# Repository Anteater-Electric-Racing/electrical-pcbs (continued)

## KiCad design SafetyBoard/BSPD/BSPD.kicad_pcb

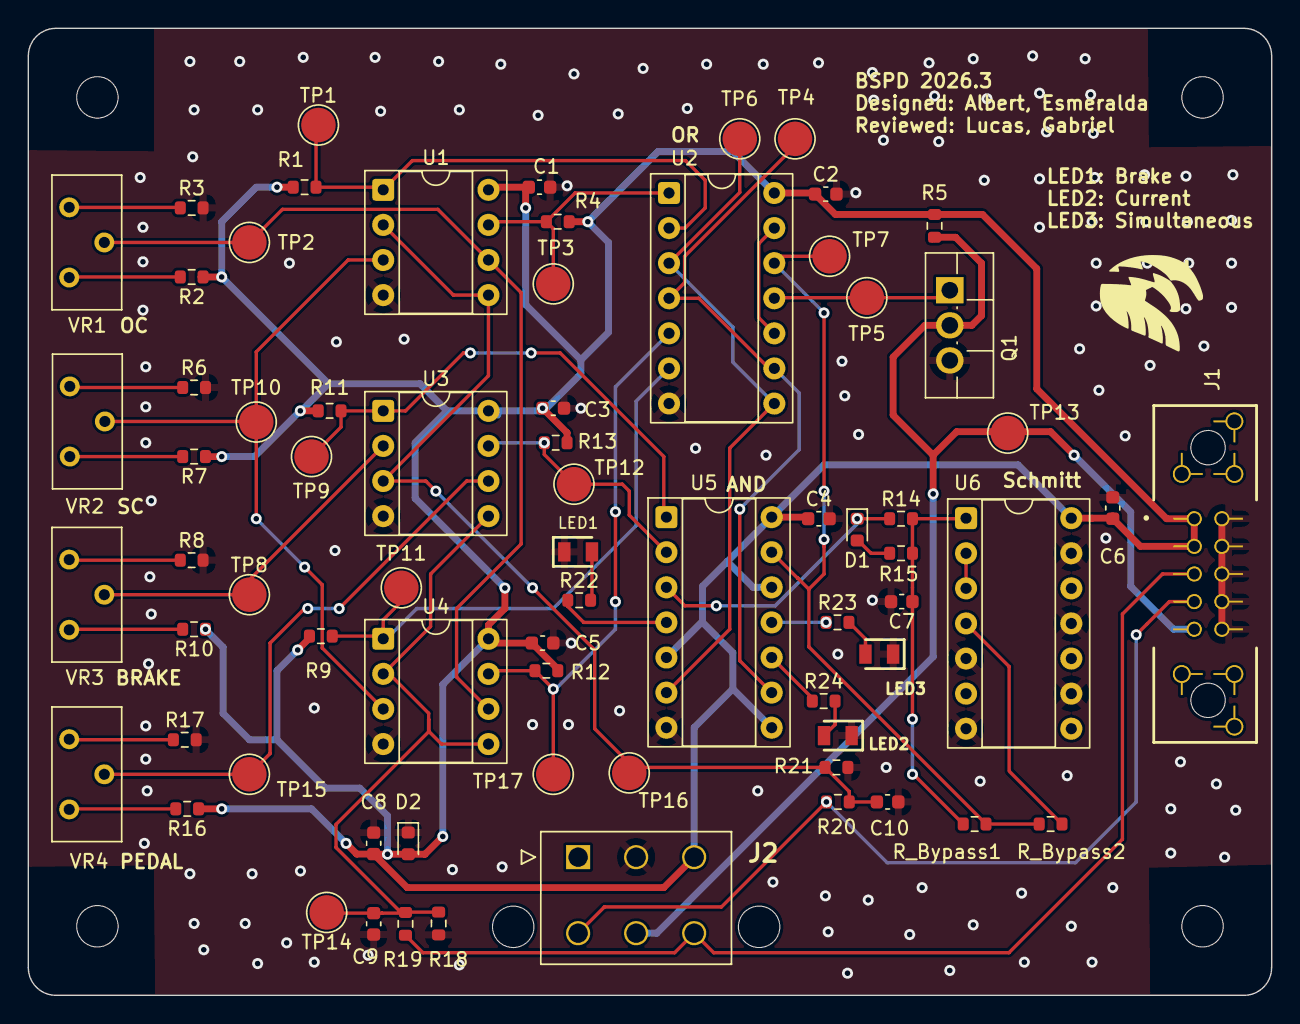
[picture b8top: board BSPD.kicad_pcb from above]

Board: 2 copper layers, 90.0 x 70.0 mm, 75 parts (0 on the bottom side), 41 nets.

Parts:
C1, C2, C3, C4, C5, C6: 0.1u; C_0603_1608Metric
C7: 3.3u; C_0603_1608Metric
C8: 10u; C_0603_1608Metric
C9, C10: 1n; C_0603_1608Metric
D1, D2: D; D_0603_1608Metric
H1, H2, H3, H4: MH; MountingHole_3mm
J1: T2M-105-01-X-D-TH-DS; SAMTEC_T2M-105-01-X-D-TH-DS
J2: 39-30-6068; 39-30-606Y
LED1, LED2, LED3: APTD2012LSYCK; LEDC2012X105N
Q1: IRLIZ44N NMOS; TO-220F-3_Vertical
R1, R4, R9, R11, R12, R13: 20k; R_0603_1608Metric
R2, R3, R6, R7, R8, R10, R16, R17: 10K; R_0603_1608Metric
R5, R22, R23, R24: 10k; R_0603_1608Metric
R14: 120k; R_0603_1608Metric
R15, R19, R20: 1k; R_0603_1608Metric
R18, R21: 500k; R_0603_1608Metric
R_Bypass1, R_Bypass2: 0; R_0603_1608Metric
TP1: B_SHORT; TestPoint_Pad_D2.5mm
TP2: OC; TestPoint_Pad_D2.5mm
TP3: B_OPEN; TestPoint_Pad_D2.5mm
TP4: P_ERROR; TestPoint_Pad_D2.5mm
TP5: FAULT_SENSED; TestPoint_Pad_D2.5mm
TP6: B_ERROR; TestPoint_Pad_D2.5mm
TP7: BOTH_ON; TestPoint_Pad_D2.5mm
TP8: BRAKE_TH; TestPoint_Pad_D2.5mm
TP9: B_APPLIED; TestPoint_Pad_D2.5mm
TP10: SC; TestPoint_Pad_D2.5mm
TP11: P_SHORT; TestPoint_Pad_D2.5mm
TP12: P_APPLIED; TestPoint_Pad_D2.5mm
TP13: BSPD_FAULT; TestPoint_Pad_D2.5mm
TP14: PEDAL; TestPoint_Pad_D2.5mm
TP15: PEDAL_TH; TestPoint_Pad_D2.5mm
TP16: BRAKE; TestPoint_Pad_D2.5mm
TP17: P_OPEN; TestPoint_Pad_D2.5mm
U1, U3, U4: LM393; DIP-8_W7.62mm_Socket
U2: 4071 4 Channel 2 Input OR gate; DIP-14_W7.62mm_Socket
U5: 4081 AND Gate; DIP-14_W7.62mm_Socket
U6: 40106 Inverter; DIP-14_W7.62mm_Socket
VR1, VR2, VR3, VR4: 3296Y-11-103LF; Potentiometer_Bourns_3296Y_Vertical

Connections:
+12V: C1.1, C2.1, C3.1, C4.1, C5.1, C6.1, C8.1, D2.2 (A), J1.01, J1.03, J2.3, R1.2, R2.1, R4.2, R5.1, R7.1, R9.2, R10.1, R11.2, R12.2, R13.2, R16.1, U1.8 (V+), U2.14 (VDD), U3.8 (V+), U4.8 (V+), U5.5, U5.8, U5.12, U5.14 (VDD), U6.14 (VDD)
BOTH_ON: R_Bypass1.2, R_Bypass2.1, TP7.1, U2.12, U5.13
BRAKE: C10.1, R20.1, R21.2, TP16.1, U1.2 (-), U1.5 (+), U3.3 (+)
BRAKE_APPLIED: R11.1, TP9.1, U3.1, U5.1
BRAKE_ERROR: TP6.1, U2.3, U2.8, U5.6
BRAKE_OPEN: R4.1, TP3.1, U1.7, U2.1
BRAKE_SHORT: R1.1, TP1.1, U1.1, U2.2
BRAKE_THRESHOLD: TP8.1, U3.2 (-), VR3.2 (WIPER)
BSPD_FAULT: J1.09, J2.5, Q1.2 (D), R5.2, TP13.1
B_IN: J1.07, J2.4, R20.2
CURRENT: C9.1, R18.2, R19.1, TP14.1, U3.5 (+), U4.2 (-), U4.5 (+)
C_IN: J1.05, J2.6, R19.2
FAULT_SENSED: Q1.1 (G), TP5.1, U2.11
GND: C1.2, C2.2, C3.2, C4.2, C5.2, C6.2, C7.2, C8.2, C9.2, C10.2, D2.1 (K), J1.02, J1.04, J1.06, J1.08, J1.10, J2.2, LED1.1 (K), LED2.1 (K), LED3.1 (K), Q1.3 (S), R3.2, R6.2, R8.2, R17.2, R18.1, R21.1, U1.4 (V-), U2.7 (VSS), U3.4 (V-), U4.4 (V-), U5.7 (VSS), U6.5, U6.7 (VSS), U6.9, U6.11, U6.13
unnamed: C7.1, R14.2, R15.2, R_Bypass1.1, U6.1
unnamed: D1.2 (A), R15.1
unnamed: D1.1 (K), R14.1, U5.3
unnamed: LED1.2 (A), R22.2
unnamed: LED2.2 (A), R24.2
unnamed: LED3.2 (A), R23.2
unnamed: R22.1, U5.4
unnamed: R23.1, U5.11
unnamed: R24.1, U5.10
unnamed: R_Bypass2.2, U6.4
unnamed: U2.10, U2.13
unnamed: U6.2, U6.3
unnamed: R3.1, VR1.1 (CCW)
unnamed: R2.2, VR1.3 (CW)
unnamed: R6.1, VR2.1 (CCW)
unnamed: R7.2, VR2.3 (CW)
unnamed: R8.1, VR3.1 (CCW)
unnamed: R10.2, VR3.3 (CW)
unnamed: R17.1, VR4.1 (CCW)
unnamed: R16.2, VR4.3 (CW)
OPEN_CIRCUIT: TP2.1, U1.6 (-), U4.6 (-), VR1.2 (WIPER)
PEDAL_APPLIED: R13.1, TP12.1, U3.7, U5.2
PEDAL_ERROR: TP4.1, U2.4, U2.9, U5.9
PEDAL_OPEN: R12.1, TP17.1, U2.5, U4.7
PEDAL_SHORT: R9.1, TP11.1, U2.6, U4.1
PEDAL_THRESHOLD: TP15.1, U3.6 (-), VR4.2 (WIPER)
SHORT_CIRCUIT: TP10.1, U1.3 (+), U4.3 (+), VR2.2 (WIPER)

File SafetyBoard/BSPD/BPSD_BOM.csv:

"Reference","Value","Datasheet","Footprint","Qty","DNP","Manufacturer_Part_Number","Manufacturer_Name"
"J2","39-30-6068","https://www.molex.com/pdm_docs/sd/039306048_sd.pdf","39-30:39-30-606Y","1","","39-30-6068","Molex"
"C1,C2,C3,C4,C5,C6","0.1u","https://www.mouser.com/ProductDetail/Murata-Electronics/GRT1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","Capacitor_SMD:C_0603_1608Metric","6","","GRT188R71H104KE13D ","Murata Electronics"
"C7","3.3u","https://www.digikey.com/en/products/detail/kemet/C0603C335K9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","Capacitor_SMD:C_0603_1608Metric","1","","C0603C335K9PACTU","Kemet"
"C8","10u","https://www.digikey.com/en/products/detail/murata-electronic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","Capacitor_SMD:C_0603_1608Metric","1","","GRM188R60J106KE47D","Murata Electronics"
"C9,C10","1n","https://www.mouser.com/ProductDetail/Murata-Electronics/GRM1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","Capacitor_SMD:C_0603_1608Metric","2","","GRM188R72E102KW07D","Murata Electronics "
"D1,D2","D","https://www.digikey.com/en/products/detail/bourns-inc/CD0603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","Diode_SMD:D_0603_1608Metric","2","","CD0603-B0240R","Bourns Inc"
"H1,H2,H3,H4","MH","~","MountingHole:MountingHole_3mm","4","","",""
"U2","4071 4 Channel 2 Input OR gate","http://www.intersil.com/content/dam/Intersil/documents/cd40/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","Package_DIP:DIP-14_W7.62mm_Socket","1","","CD4071BE","Texas Instruments"
"U5","4081 AND Gate","http://www.intersil.com/content/dam/Intersil/documents/cd40/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","Package_DIP:DIP-14_W7.62mm_Socket","1","","CD4081BEE4","Texas Instruments"
"U6","40106 Inverter","https://assets.nexperia.com/documents/data-sheet/HEF40106B.pdf","Package_DIP:DIP-14_W7.62mm_Socket","1","","CD40106BE ","Texas Instruments"
"U1,U3,U4","LM393","http://www.ti.com/lit/ds/symlink/lm393.pdf","Package_DIP:DIP-8_W7.62mm_Socket","3","","LM393P","Texas Instruments"
"Q1","IRLIZ44N NMOS","http://www.irf.com/product-info/datasheets/data/irliz44n.pdf","Package_TO_SOT_THT:TO-220F-3_Vertical","1","","IRLZ44NPBF","Infineon"
"VR1,VR2,VR3,VR4","3296Y-11-103LF","https://www.bourns.com/pdfs/3296.pdf","Potentiometer_THT:Potentiometer_Bourns_3296Y_Vertical","4","","3296Y-11-103LF","Bourns"
"R1,R4,R9,R11,R12,R13","20k","https://www.digikey.com/en/products/detail/yageo/RC0603FR-07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","Resistor_SMD:R_0603_1608Metric","6","","RC0603FR-0720KL","Yageo"
"R2,R3,R6,R7,R8,R10,R16,R17","10K","https://www.digikey.com/en/products/detail/yageo/RC0603FR-07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","Resistor_SMD:R_0603_1608Metric","8","","RC0603FR-0710KL","Yageo"
"R5,R22,R23,R24","10k","https://www.digikey.com/en/products/detail/yageo/RC0603FR-07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","Resistor_SMD:R_0603_1608Metric","4","","RC0603FR-0720KL","Yageo"
"R14","120k","https://www.digikey.com/en/products/detail/yageo/RC0603FR-07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","Resistor_SMD:R_0603_1608Metric","1","","RC0603FR-07120KL","Yageo"
"R15,R19,R20","1k","https://www.digikey.com/en/products/detail/yageo/RC0603FR-07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","Resistor_SMD:R_0603_1608Metric","3","","RC0603FR-071KL","Yageo"
"R18,R21","500k","https://www.digikey.com/en/products/detail/yageo/RC0603FR-07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","Resistor_SMD:R_0603_1608Metric","2","","RC0603FR-07500KL","Yageo"
"R_Bypass1,R_Bypass2","0","~","Resistor_SMD:R_0603_1608Metric","2","","","Yageo"
"LED1,LED2,LED3","APTD2012LSYCK","http://www.kingbrightusa.com/images/catalog/SPEC/APTD2012LSYCK.pdf","SMALL_LED:LEDC2012X105N","3","","APTD2012LSYCK","Kingbright"
"J1","T2M-105-01-X-D-TH-DS","","T2M_105:SAMTEC_T2M-105-01-X-D-TH-DS","1","","T2M-105-01-X-D-TH-DS","Samtec Inc."
"TP1","B_SHORT","~","TestPoint:TestPoint_Pad_D2.5mm","1","","",""
"TP2","OC","~","TestPoint:TestPoint_Pad_D2.5mm","1","","",""
"TP3","B_OPEN","","TestPoint:TestPoint_Pad_D2.5mm","1","","",""
"TP4","P_ERROR","~","TestPoint:TestPoint_Pad_D2.5mm","1","","",""
"TP5","FAULT_SENSED","~","TestPoint:TestPoint_Pad_D2.5mm","1","","",""
"TP6","B_ERROR","~","TestPoint:TestPoint_Pad_D2.5mm","1","","",""
"TP7","BOTH_ON","~","TestPoint:TestPoint_Pad_D2.5mm","1","","",""
"TP8","BRAKE_TH","~","TestPoint:TestPoint_Pad_D2.5mm","1","","",""
"TP9","B_APPLIED","~","TestPoint:TestPoint_Pad_D2.5mm","1","","",""
"TP10","SC","~","TestPoint:TestPoint_Pad_D2.5mm","1","","",""
"TP11","P_SHORT","~","TestPoint:TestPoint_Pad_D2.5mm","1","","",""
"TP12","P_APPLIED","~","TestPoint:TestPoint_Pad_D2.5mm","1","","",""
"TP13","BSPD_FAULT","~","TestPoint:TestPoint_Pad_D2.5mm","1","","",""
"TP14","PEDAL","~","TestPoint:TestPoint_Pad_D2.5mm","1","","",""
"TP15","PEDAL_TH","~","TestPoint:TestPoint_Pad_D2.5mm","1","","",""
"TP16","BRAKE","~","TestPoint:TestPoint_Pad_D2.5mm","1","","",""
"TP17","P_OPEN","~","TestPoint:TestPoint_Pad_D2.5mm","1","","",""

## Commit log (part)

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2025-11-13 Add standardized PCB structure with RTM and TSSI folders
2025-11-14 RTM KiCad Upload
2025-11-14 RTM File update
2025-11-20 PCC addition
2025-11-20 Create Kicad
2025-11-20 Create tempp
2025-11-20 Create temp
2025-11-20 Create tem
2025-11-20 Add Updated TSSI 2026.1
2025-12-02 2026.1 fixed vbias, removed nmos after r9, r10/r8 increased
2025-12-02 2026.1 fixed vbias, removed nmos after r9, r10/r8 increase
2025-12-02 schematic pdf
2025-12-22 Add PDB pcb
2025-12-22 Silkscreen pin assignment now easier
2025-12-23 Restored step files
2025-12-28 Updated throttle sensors, marked 24V components DNP
2025-12-28 Added labels for every net
2026-01-05 Started labeling each pin
2026-01-07 Combined break pressure into Throttle sensor
2026-01-07 Added labels of possibly removeing 3V3 line
2026-01-08 added BSPD v1
2026-01-08 pcb rules test
2026-01-08 Add 2026.2 TSSI
2026-01-08 Create 2026.2 Kicad
2026-01-08 Add TSSI 2026.2
2026-01-08 Create mosfet
2026-01-08 Add TSSI2026.2
2026-01-09 update kicad checklist
2026-01-09 draft2
2026-01-10 Added more silkscreen labels
2026-01-11 ver1 1/10/2026
2026-01-11 Added 24V line back
2026-01-13 Updated RTM silkscreen
2026-01-17 Latch Board Added
2026-01-19 Update BSPD documentation with parts list and corrections
2026-01-21 2026.1 RTM modifications
    includes justification for optocoupler change
2026-01-26 Create 2026.2CCM
    temp folder until I'm able to modify the CCM folder (unless this becomes the actual CCM folder). This temp folder holds the newest CCMv3 files as of 1/25/26
2026-01-26 Delete 2026.2CCM
    needed to make folder
2026-01-26 Create 2026CCM folder
    temp folder until I'm able to modify the other CCM folder (unless this becomes the actual CCM folder). This temp folder holds the newest CCMv3 files as of 1/25/26
2026-01-26 2026.2 CCMv3
    temp folder until I can modify the actual CCM folder. added sensors, changed pin assignment on Teensy, fixed speaker amplifier. Documentation of modifications included.
2026-01-26 moved to correct temp folder
2026-01-26 not needed
2026-01-28 adding new BSPD version as well as latch
2026-02-01 Update TSSI_2026.2
    Removed 12V for lights and condensed to 2 pin for one light and the other
2026-02-02 Add silkscreen connectors
2026-02-02 connected remaining pins to gnd
2026-02-02 add gerber files
2026-02-05 Add silkscreen
2026-02-05 add PCIE stuff
2026-02-09 RTM with Revisions told by Gabe
2026-02-10 corrected biasing network, moved Vin trace
    Vin trace stays out of electrical isolation zone
2026-02-10 Update documentation
2026-02-10 Added plated mounting holes, fixed diode
2026-02-10 Made quick changes: updated fuse footprint
2026-02-11 Change TSSI2026.3
    Deleted the whole schematic ong
2026-02-11 Finish Latch 2026.21
    Vasily did this :)
2026-02-11 Add Logo
2026-02-12 Gerber Files
2026-02-12 Updated silkscreen based on Gabe's revisions
2026-02-12 Shink overall board size for PDB
2026-02-12 Added logo to front silkscreen
2026-02-13 bspd v3 plus documentation
2026-02-13 adding logo plus updating documentation
2026-02-13 Add Logo again
2026-02-16 Updated silkscreen based on Gabe's revisions #2
    Fixed missing resistor (R15) on layout
2026-02-21 3d files
2026-02-21 export step
2026-02-21 add Molex Step Files
2026-02-21 Add latch step file
2026-02-21 PDB: Removed most 5V fuses, made board size smaller
2026-02-22 file tinkering for 3d
2026-02-24 reorganizing ccm folders
2026-02-24 Revert "reorganizing ccm folders"
    This reverts commit 4ae5fa8156d4e531640948b4a7b079df29438b2f.
2026-02-24 reorganizing ccm folders
    unlinked old ccm submodule, made new ccm folder, added ccm v2 to it as 2026.1 and ccm v3 as 2026.2
2026-02-24 Revert "reorganizing ccm folders"
    This reverts commit c6433f84ad807e394f1869382292bc8514728ac1.
2026-02-26 Major changes for PDB schematic
2026-02-26 Moved .gitignore from PDB to root
2026-02-28 Rename bbc/Hi_board_bbc1.kicad_prl to bbc/export1/Hi_board_bbc1.kicad_prl
2026-02-28 Add Hi_board_bbc1.kicad_pro to export1 directory
2026-02-28 Add Hi_board_bbc1.kicad_sch to export1 directory
2026-02-28 Add fp-info-cache to export1 directory
2026-02-28 Rename bbc/hi_bbc1_export.zip to bbc/export1/hi_bbc1_export.zip
2026-02-28 Remove lock file for Hi_board_bbc1 PCB
2026-02-28 Rename bbc/~Hi_board_bbc1.kicad_sch.lck to bbc/export1/~Hi_board_bbc1.kicad_sch.lck
2026-02-28 Update and rename bbc/sym-lib-table to bbc/libraries/sym-lib-table
2026-02-28 Add libraryBBC.kicad_sym to export2 directory
2026-02-28 Move sym-lib-table to export2 directory
2026-02-28 Update GLVMP_Banana_Jack.kicad_mod file location
2026-03-02 adding test plan draft
2026-03-02 adding test plan
2026-03-02 adding rules scripts
2026-03-07 added BSPD testing report
2026-03-07 added BSPD testing report v2
2026-03-07 editing test report format
2026-03-08 Redesign TSSI
2026-03-08 slight Tweaks again
2026-03-10 Changed all NMOS to GDS
2026-03-10 Swapped NMOS at bottom
2026-03-10 swaped pins on relay
2026-03-12 Rename bbc/4Pin Deutsch Connector.SLDPRT to bbc/ROC_CAD /4Pin Deutsch Connector.SLDPRT
2026-03-12 Rename bbc/BBC Assembly.SLDASM to bbc/ROC_CAD/BBC Assembly.SLDASM
2026-03-12 Rename 4Pin Deutsch Connector.SLDPRT to 4Pin Deutsch Connector.SLDPRT
2026-03-12 Rename bbc/BBC Container.SLDPRT to bbc/ROC_CAD/BBC Container.SLDPRT
2026-03-12 Rename bbc/Master Switch.SLDPRT to bbc/ROC_CAD/Master Switch.SLDPRT
2026-03-12 Rename bbc/Speaker.SLDPRT to bbc/ROC_CAD/Speaker.SLDPRT
2026-03-12 Update BSPD schematic and add BOM
2026-03-12 Add LATCH_BOM.csv
2026-03-12 Add TSSI BOM
2026-03-13 Deleted extra trace
2026-03-14 fixed comparator pinouts and pcb layout
2026-03-19 Reduced PDB size, power planes just started
2026-03-23 Finalized PDB silkscreen
2026-03-25 PDB Edits: Fixed 3D model, init README.md
2026-03-25 PDB: Started rough draft of README.md
2026-03-26 Add PCC
2026-03-26 deleted redundant PCC folder
2026-03-27 ARCHIVE: Snapshot of folder-based structure before flattening
2026-03-27 REORG: Flattened folder structure. we now use tags after every order to mark a finalized version. Keep overriding and pushing to main. Do not use branches unless you have a good reason to.
2026-03-27 Remove CCM submodule
2026-03-27 Changed a buncha stuff on other ppl's board. established new branch
2026-03-28 day 2 grind
2026-03-28 hopefully this lets avadi pull
2026-03-29 rough layout done
2026-03-31 Fixed Copper Zones on Resistor Divider, Fixed Mounting Holes and Placement, adjusted traces
2026-03-31 Acid Traps
2026-03-31 Lucas Out
2026-03-31 silkscreen and some fuses or something
2026-04-01 ccm v2.1
    new speaker amp, fixed keyswitch control
2026-04-01 I think think this is final but need to defuck the BOM
2026-04-01 PCC rev added port
2026-04-03 moved around connectors
2026-04-04 Safety Board: added BOM and updated schematics
2026-04-04 ChargerBoard Born and done
2026-04-04 updates I think
2026-04-06 silkscreen, last touches time to order
2026-04-06 gerber added
2026-04-06 silkscreen finish touches
2026-04-06 fuse holders added
2026-04-07 Right-side realignment
2026-04-07 Redimensioned, New Layout
2026-04-08 Traces Check 1
2026-04-08 Traces Check 2
2026-04-08 Male connector models added
2026-04-09 Connector spacing updated
2026-04-09 Connector spacing update 2
2026-04-09 Increased trace width
2026-04-09 Minor updates
2026-04-09 real final
2026-04-10 double checking its all pushed
2026-04-10 swapped BBC ports
2026-04-10 3d component changes
2026-04-11 deleted buggy files
2026-04-11 whoops forgot can on charger board
2026-04-30 PCCv2 started
2026-05-07 PCC finalized
2026-05-07 merged SB with main hopefully
2026-05-07 hopefully ts based
2026-05-07 fixed an error when opening SB prjct
2026-05-31 PCC was rolled back rerolled it
2026-06-15 2026 final
